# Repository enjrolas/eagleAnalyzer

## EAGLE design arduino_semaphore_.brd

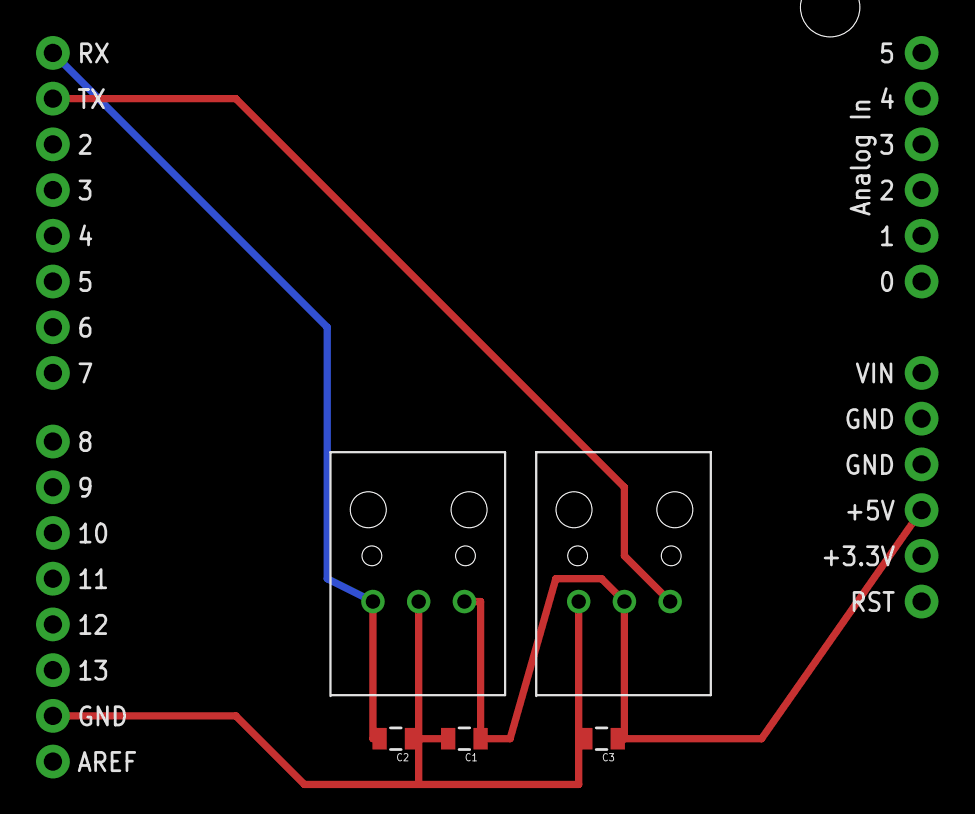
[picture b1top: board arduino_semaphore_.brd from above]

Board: 2 copper layers, 6 parts (0 on the bottom side), 4 nets.

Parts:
C1, C3: 0.1uF; 0805
C2: 30pF; 0805
U1: ARDUINO_SHIELDLABEL; DUEMILANOVE_SHIELD
U$1: DLR1160; DLR
U$2: DLT1160; DLT

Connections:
unnamed: C2.2, U1.RX, U$1.VOUT
unnamed: C1.1, C3.1, U1.5V, U$1.VCC, U$2.VCC
unnamed: C1.2, C2.1, C3.2, U1.GND@2, U$1.GND, U$2.GND
unnamed: U1.TX, U$2.VIN

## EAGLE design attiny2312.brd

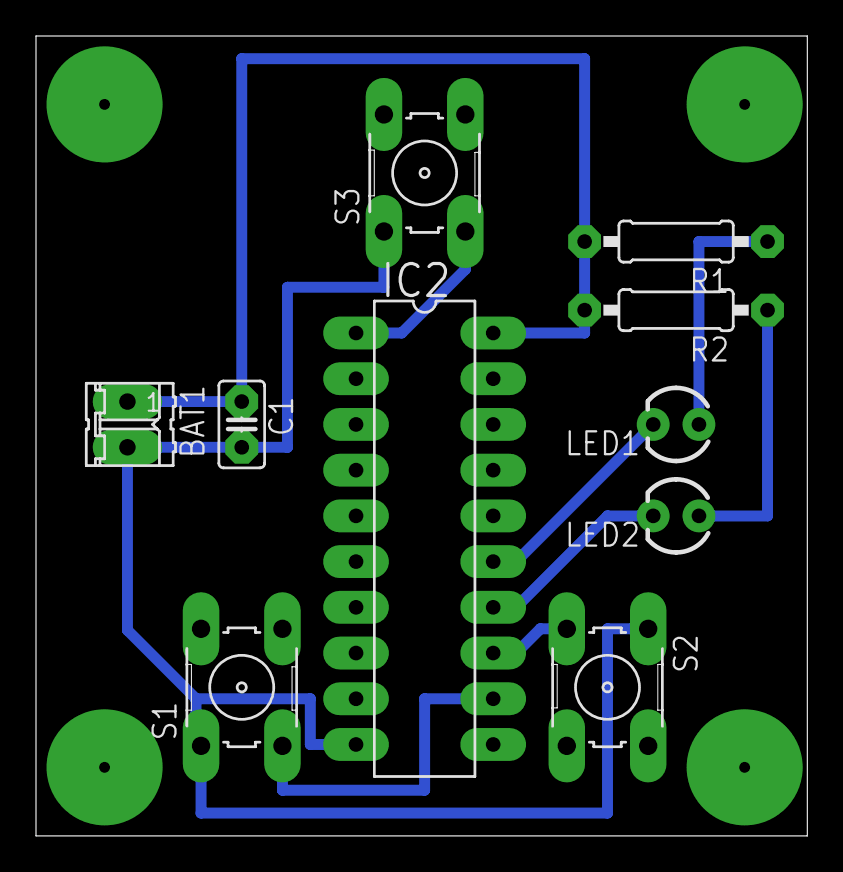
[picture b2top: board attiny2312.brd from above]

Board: 2 copper layers, 42.9 x 44.4 mm, 10 parts (0 on the bottom side), 9 nets.

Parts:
BAT1: 1.5 x 2; RELIMATE
C1: C2.5-2
IC2: AT90S2313P; DIL20
LED1, LED2: LED3MM
R1, R2: 0207/10
S1, S2, S3: B3F-10XX

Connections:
GND: BAT1.2, C1.2, IC2.10, S1.1, S2.1, S3.1
unnamed: LED1.A, R1.1
unnamed: LED2.A, R2.1
PB0: IC2.12, S1.3
PB1: IC2.13, S2.3
PB2: IC2.14, LED2.K
PB3: IC2.15, LED1.K
RESET: IC2.1, S3.3
VCC: BAT1.1, C1.1, IC2.20, R1.2, R2.2

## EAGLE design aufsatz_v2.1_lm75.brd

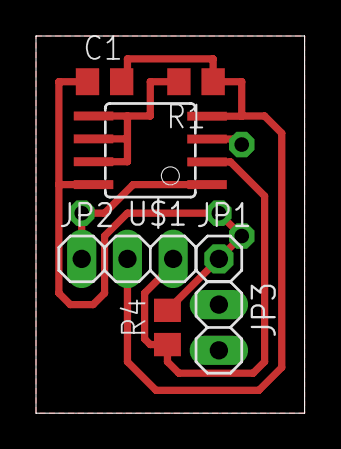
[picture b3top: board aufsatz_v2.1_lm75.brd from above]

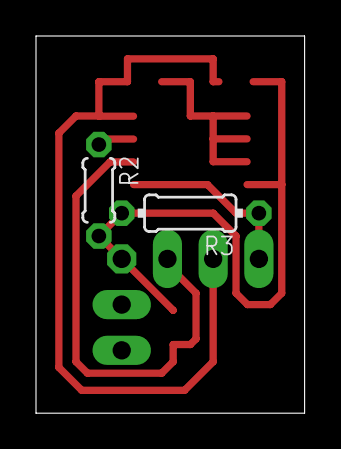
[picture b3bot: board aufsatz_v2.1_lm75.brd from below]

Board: 2 copper layers, 14.9 x 21.0 mm, 9 parts (2 on the bottom side), 6 nets.

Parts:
C1: 100n; C0805
JP1: 1X01
JP2: 1X03
JP3: 1X02
R1: 10k; R0805
R2: 10k; 0204/5
R3: 4k7; 0204/7
R4: 4k7; R0805
U$1: LM75; SOIC8

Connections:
GND: C1.2, JP2.2, R1.1, U$1.4
unnamed: R1.2, U$1.5, U$1.6, U$1.7
unnamed: R2.1, U$1.3
SCL: JP2.3, R4.1, U$1.2
SDA: JP2.1, R3.1, U$1.1
VCC: C1.1, JP1.1, R2.2, R3.2, R4.2, U$1.8

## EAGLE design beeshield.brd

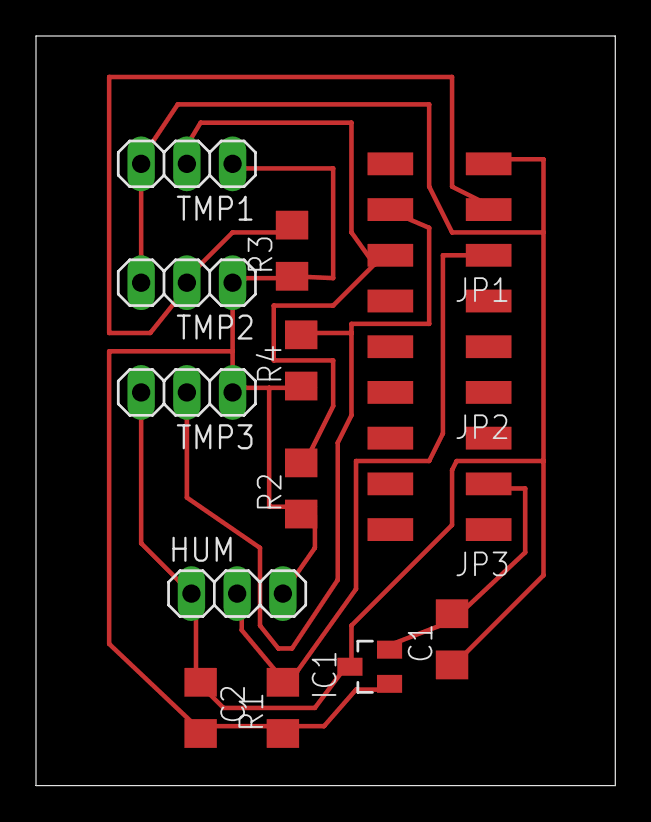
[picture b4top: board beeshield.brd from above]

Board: 2 copper layers, 32.2 x 41.6 mm, 14 parts (0 on the bottom side), 7 nets.

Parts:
C1, C2: 1206
HUM: 1X03
IC1: SOT23
JP1, JP2, JP3: 2X03SMD
R1: 10k; 1206
R2, R3, R4: 4k7; 1206
TMP1, TMP2, TMP3: 1X03

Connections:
GND: C1.1, C2.1, HUM.1, IC1.3, JP1.5, TMP1.3, TMP2.3, TMP3.3
IO0: HUM.2, JP1.1, R1.2
IO1: JP1.2, R2.2, TMP1.2
IO2: JP1.3, R3.2, TMP2.2
IO3: JP1.4, R4.2, TMP3.2
VBAT1: C1.2, IC1.2, JP3.3
VCC: C2.2, HUM.3, IC1.1, R1.1, R2.1, R3.1, R4.1, TMP1.1, TMP2.1, TMP3.1

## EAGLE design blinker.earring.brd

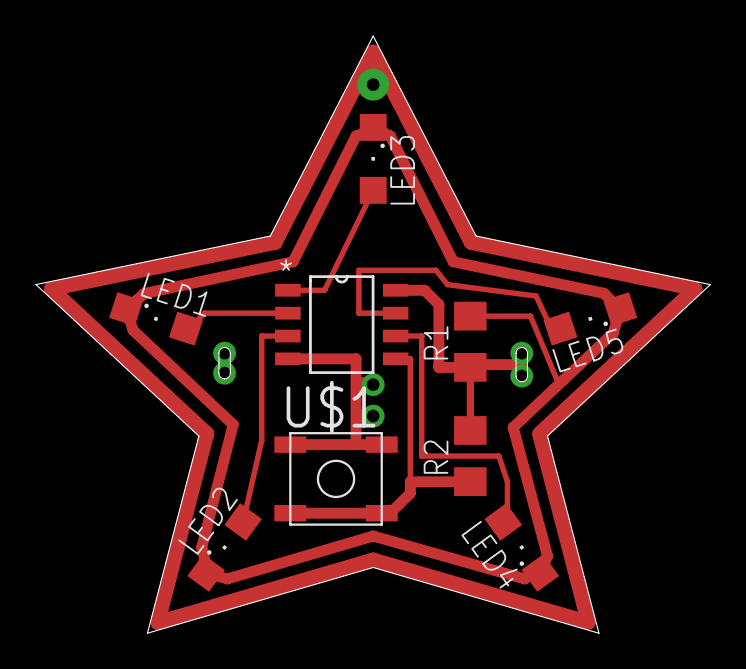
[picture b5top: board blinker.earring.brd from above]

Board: 2 copper layers, 37.5 x 33.2 mm, 9 parts (0 on the bottom side), 9 nets.

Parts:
LED1, LED2, LED3, LED4, LED5: SML1206
R1, R2: R1206
U$1: ATTINY13V-S8S1; ATTINY13A-SSU
U$3: MIMISMD; MINISMD

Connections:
unnamed: LED1.A, U$1.2
unnamed: LED2.A, U$1.3
unnamed: LED3.A, U$1.1
unnamed: LED4.A, U$1.6
unnamed: LED5.A, U$1.7
unnamed: U$1.4, U$3.P$1, U$3.P$3
unnamed: R1.1, R2.2, U$1.8
unnamed: LED1.C, LED2.C, LED3.C, LED4.C, LED5.C, R1.2
unnamed: R2.1, U$1.5, U$3.P$2, U$3.P$4

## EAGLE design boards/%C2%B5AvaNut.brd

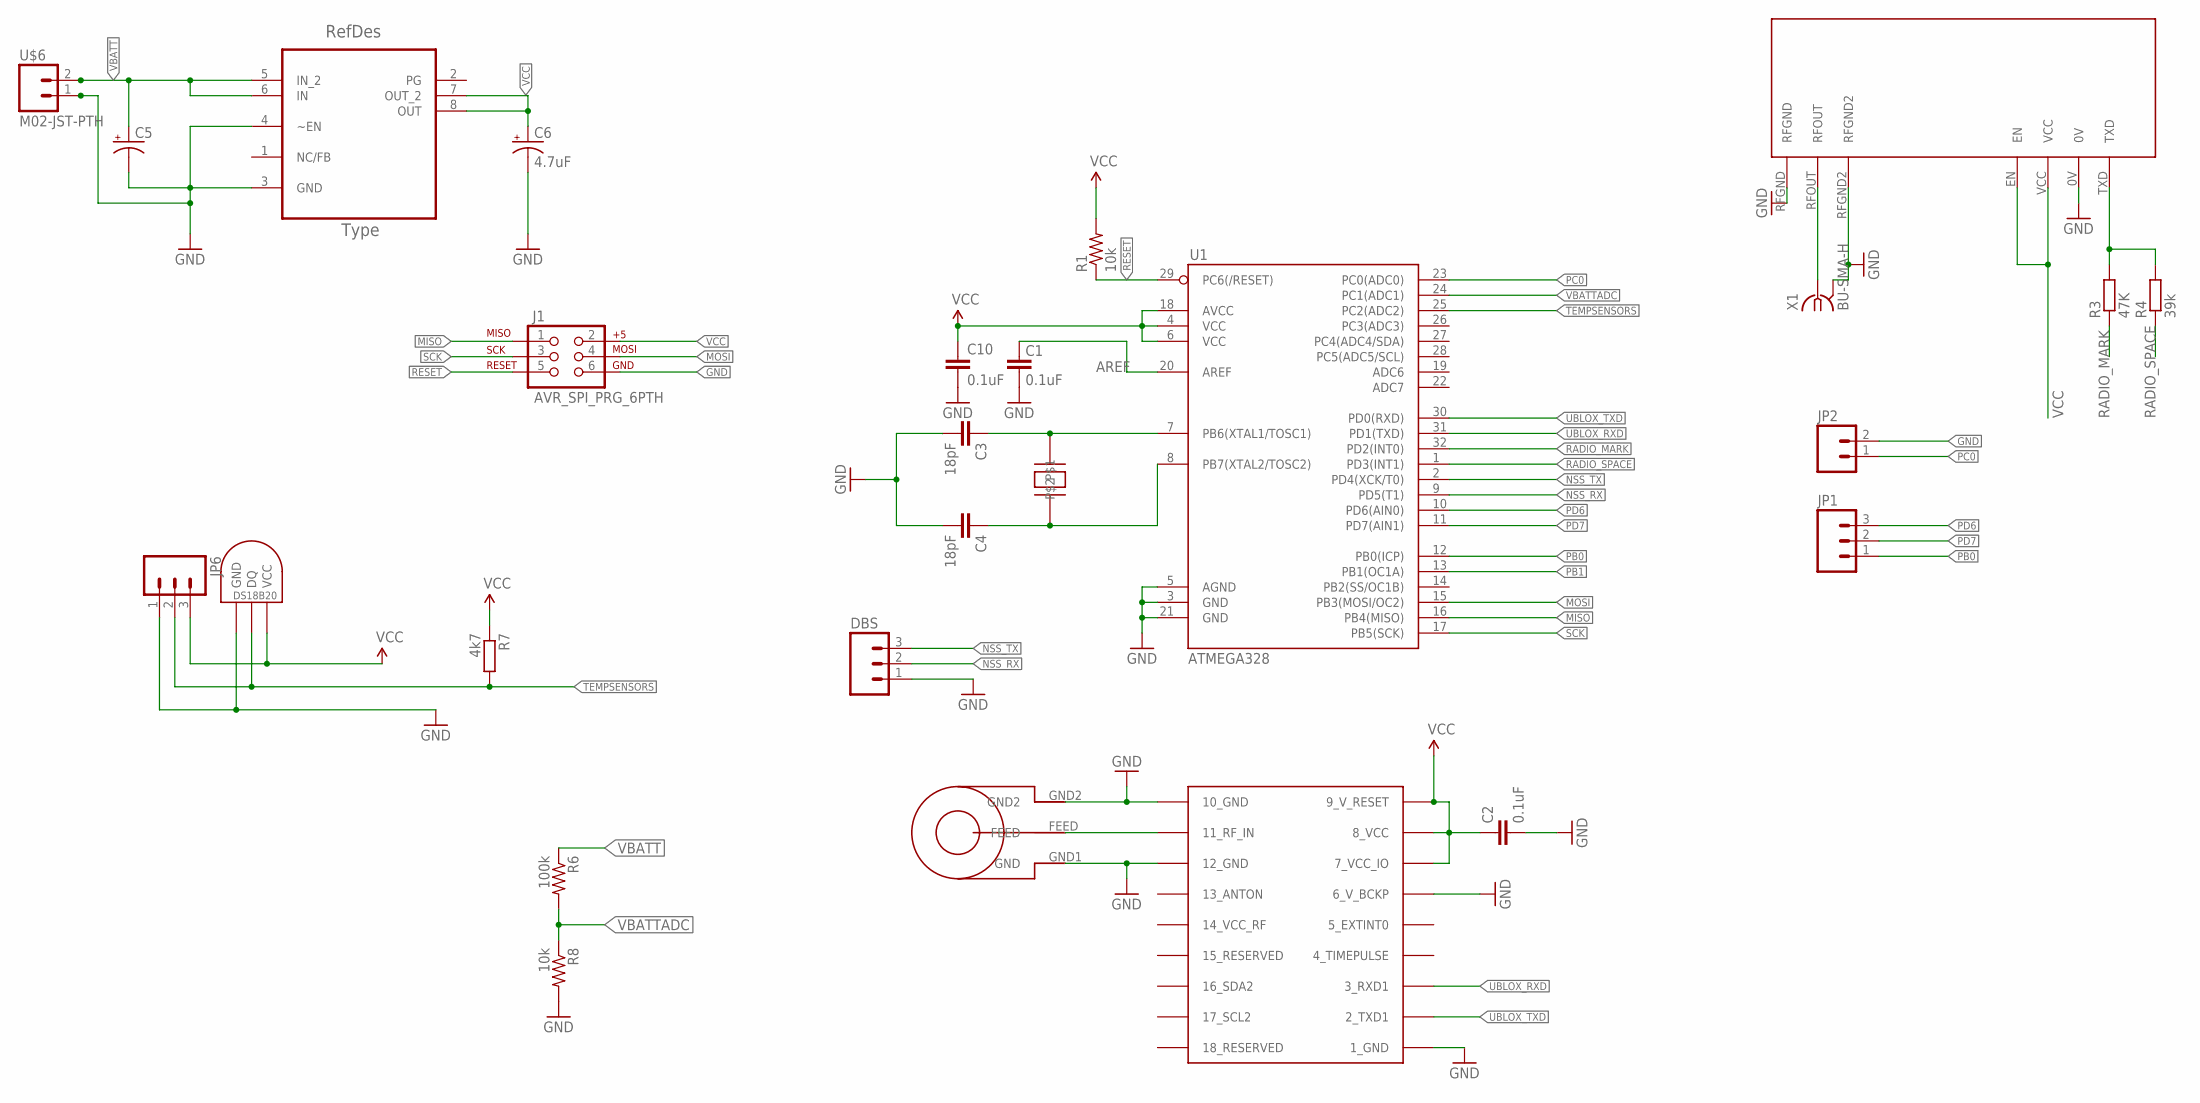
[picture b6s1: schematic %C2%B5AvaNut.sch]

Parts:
C1, C2, C10: 0.1uF; 0402-CAP
C3, C4: 18pF; 0402-CAP
C5: CAP_POL1206-KIT; EIA3216-KIT
C6: 4.7uF; EIA3216-KIT
DBS: M03PTH; 1X03
J1: AVR_SPI_PRG_6PTH; 2X3
JP1: M03POGO_PIN_HOLES_ONLY; 1X03_PP_HOLES_ONLY
JP2: M02POGO_PIN_HOLES_ONLY; 1X02_PP_HOLES_ONLY
JP6: M03JST-PTH; JST-3-PTH
NTX2TEMP: DS1821; DS18B20_SOIC
R1, R8: 10k; 0402-RES
R3: 47K; R0805
R4: 39k; R0805
R6: 100k; 0402-RES
R7: 4k7; R0805
U1: ATMEGA328; TQFP32-08
U2: TPS76633D; SOIC127P600X175-8N
U$1: UBLOX_MAX-6
U$2: ABRACON_ABM3_CRYSTAL
U$3: SARANTEL-SR1202
U$4: NTX2
U$6: M02-JST-PTH
X1: BU-SMA-H

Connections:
AREF: C1.2, U1.20 (AREF)
GND: C1.1, C2.2, C3.2, C4.2, C5.C (-), C6.C (-), C10.2, DBS.1, J1.6, JP2.2, JP6.1, NTX2TEMP.GND, R8.2, U1.3 (GND), U1.5 (AGND), U1.21 (GND), U2.3 (GND), U2.4 (~EN), U$1.1_GND, U$1.6_V_BCKP, U$1.10_GND, U$1.12_GND, U$3.GND1 (GND), U$3.GND2, U$4.0V, U$4.RFGND, U$4.RFGND2, U$6.1, X1.2 (GND), X1.3 (GND), X1.4 (GND), X1.5 (GND)
MISO: J1.1, U1.16 (PB4(MISO))
MOSI: J1.4, U1.15 (PB3(MOSI/OC2))
unnamed: U$4.RFOUT, X1.1
unnamed: R3.2, R4.2, U$4.TXD
unnamed: U$1.11_RF_IN, U$3.FEED
unnamed: C3.1, U1.7 (PB6(XTAL1/TOSC1)), U$2.P$2
unnamed: C4.1, U1.8 (PB7(XTAL2/TOSC2)), U$2.P$1
NSS_RX: DBS.2, U1.9 (PD5(T1))
NSS_TX: DBS.3, U1.2 (PD4(XCK/T0))
PB0: JP1.1, U1.12 (PB0(ICP))
PB1: U1.13 (PB1(OC1A))
PC0: JP2.1, U1.23 (PC0(ADC0))
PD6: JP1.3, U1.10 (PD6(AIN0))
PD7: JP1.2, U1.11 (PD7(AIN1))
RADIO_MARK: R3.1, U1.32 (PD2(INT0))
RADIO_SPACE: R4.1, U1.1 (PD3(INT1))
RESET: J1.5, R1.1, U1.29 (PC6(/RESET))
SCK: J1.3, U1.17 (PB5(SCK))
TEMPSENSORS: JP6.2, NTX2TEMP.DQ, R7.2, U1.25 (PC2(ADC2))
UBLOX_RXD: U1.31 (PD1(TXD)), U$1.3_RXD1
UBLOX_TXD: U1.30 (PD0(RXD)), U$1.2_TXD1
VBATT: C5.A (+), R6.1, U2.5 (IN_2), U2.6 (IN), U$6.2
VBATTADC: R6.2, R8.1, U1.24 (PC1(ADC1))
VCC: C2.1, C6.A (+), C10.1, J1.2, JP6.3, NTX2TEMP.VCC, R1.2, R7.1, U1.4 (VCC), U1.6 (VCC), U1.18 (AVCC), U2.7 (OUT_2), U2.8 (OUT), U$1.7_VCC_IO, U$1.8_VCC, U$1.9_V_RESET, U$4.EN, U$4.VCC

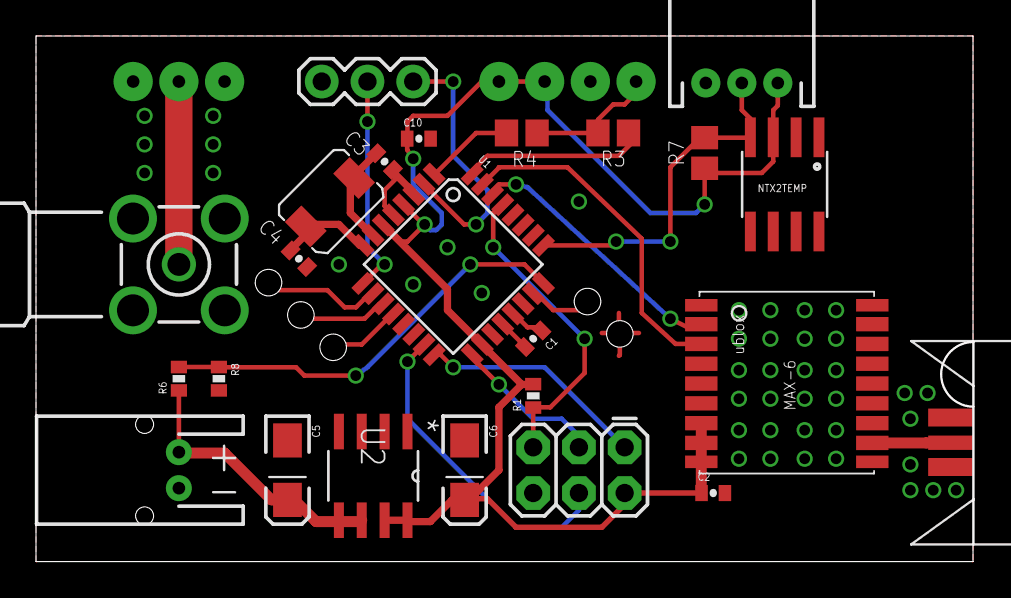
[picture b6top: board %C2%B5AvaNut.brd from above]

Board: 2 copper layers, 52.1 x 29.2 mm, 27 parts (1 on the bottom side), 25 nets.

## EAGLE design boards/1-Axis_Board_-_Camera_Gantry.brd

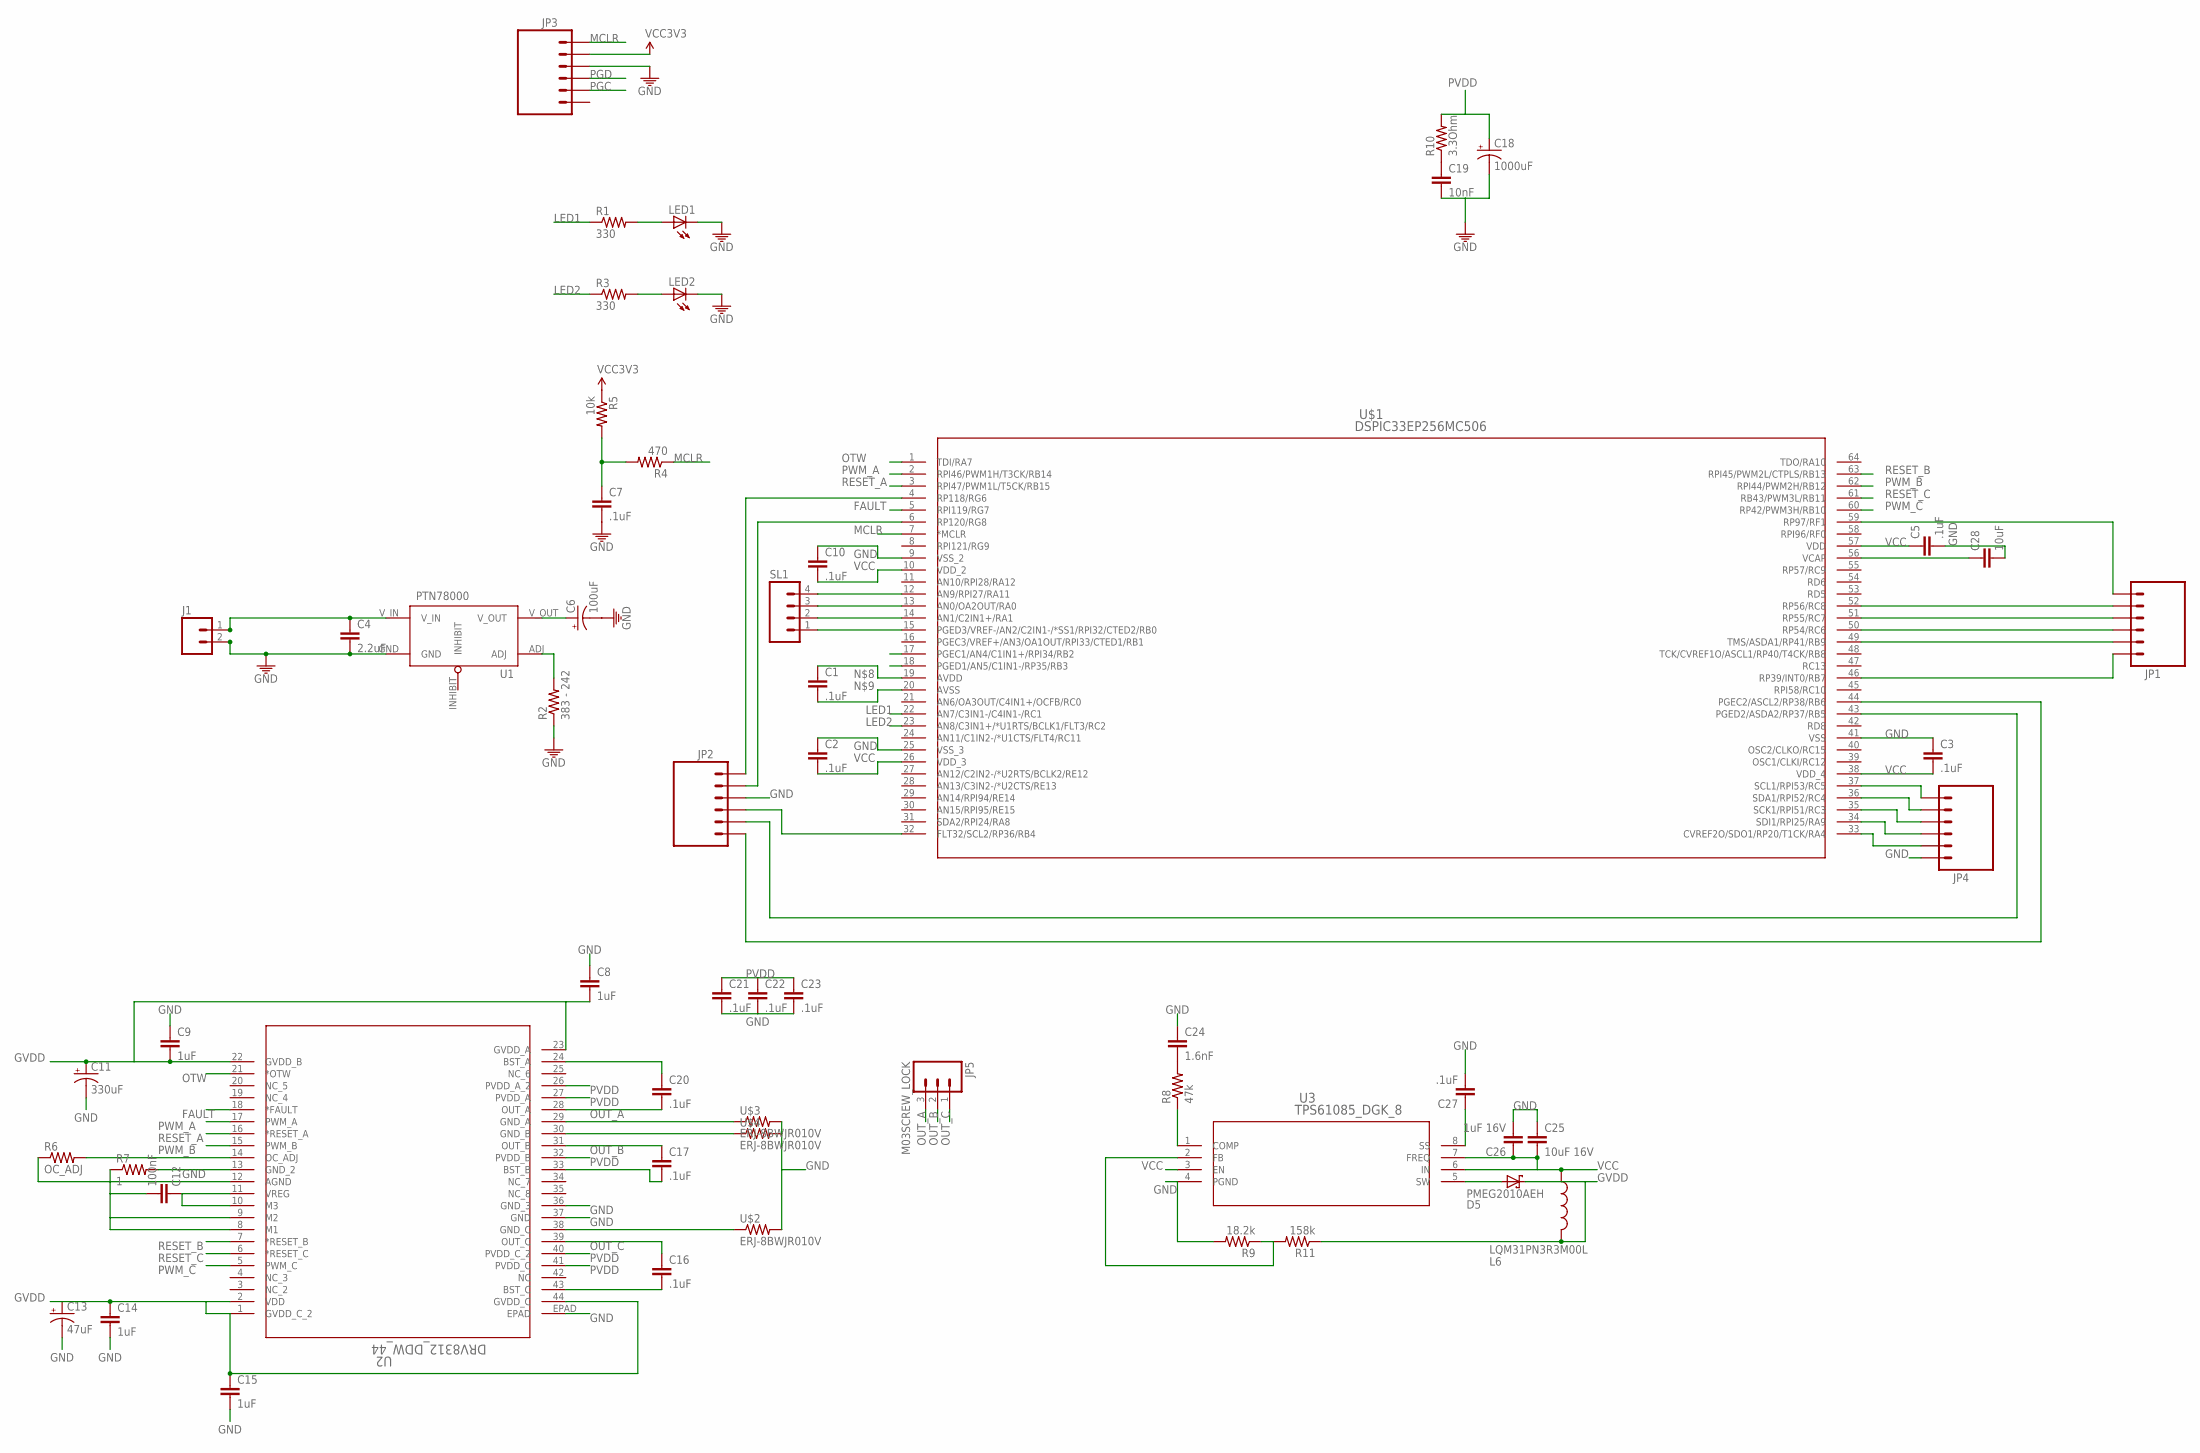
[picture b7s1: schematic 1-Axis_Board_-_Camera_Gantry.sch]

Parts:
C1, C2, C3, C5, C7, C10, C16, C17, C20, C21, C22, C23, C27: .1uF; 0805
C4: 2.2uF; 1206
C6: 100uF; CPOL-RADIAL-100UF-25V
C8, C9, C14, C15: 1uF; 0805
C11: 330uF; CPOL-RADIAL-1000UF-25V
C12: 100nF; 0805
C13: 47uF; CPOL-RADIAL-1000UF-25V
C18: 1000uF; CPOL-RADIAL-1000UF-25V
C19: 10nF; 0805
C24: 1.6nF; 0805
C25: 10uF 16V; 1206
C26: 1uF 16V; 0805
C28: 10uF; 1206
D5: PMEG2010AEH; SOD-123
J1: M023.5MM-NO_SILK; SCREWTERMINAL-3.5MM-2-NS
JP1, JP2, JP3, JP4: M06LOCK; 1X06_LOCK
JP5: M03SCREW_LOCK; SCREWTERMINAL-3.5MM-3_LOCK.007S
L6: LQM31PN3R3M00L; 1206
LED1, LED2: LED1206; LED-1206
R1, R3: 330; 0805
R2: 383 - 242; 0805
R4: 470; 0805
R5: 10k; 0805
R6: OC_ADJ; 0805
R7: 1; 0805
R8: 47k; 0805
R9: 18.2k; 0805
R10: 3.3Ohm; 0805
R11: 158k; 0805
SL1: M04LOCK; 1X04_LOCK
U1: PTN78000
U2: DRV8312_DDW_44; DDW44_8P26X4P31
U3: TPS61085_DGK_8; DGK8
U$1: DSPIC33EP256MC506; QFP64-10X10MC
U$2, U$3, U$4: ERJ-8BWJR010V; 1206

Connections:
FAULT: U2.18 (*FAULT), U$1.5 (RPI119/RG7)
GND: C2.1, C3.1, C4.2, C5.2, C6.2 (-), C7.2, C8.1, C9.1, C10.1, C11.2 (-), C13.2 (-), C14.2, C15.2, C18.2 (-), C19.2, C21.2, C22.2, C23.2, C24.1, C25.1, C26.2, C27.2, C28.2, J1.2 (1), JP2.3, JP3.3, JP4.1, LED1.C, LED2.C, R2.1, R7.2, R9.2, U1.GND, U2.13 (GND_2), U2.36 (GND_3), U2.37 (GND), U2.EPAD, U3.4 (PGND), U$1.9 (VSS_2), U$1.25 (VSS_3), U$1.41 (VSS), U$2.2, U$3.2, U$4.2
GVDD: C8.2, C9.2, C11.1 (+), C13.1 (+), C14.1, C15.1, D5.C, L6.2, R11.1, U2.1 (GVDD_C_2), U2.2 (VDD), U2.22 (GVDD_B), U2.23 (GVDD_A), U2.44 (GVDD_C)
LED1: R1.1, U$1.22 (AN7/C3IN1-/C4IN1-/RC1)
LED2: R3.1, U$1.23 (AN8/C3IN1+/*U1RTS/BCLK1/FLT3/RC2)
MCLR: JP3.1, R4.1, U$1.7 (*MCLR)
unnamed: LED1.A, R1.2
unnamed: C7.1, R4.2, R5.2
unnamed: LED2.A, R3.2
unnamed: U2.38 (GND_C), U$2.1
unnamed: U2.29 (GND_A), U$3.1
unnamed: R2.2, U1.ADJ
unnamed: U2.30 (GND_B), U$4.1
unnamed: C1.1, U$1.19 (AVDD)
unnamed: C1.2, U$1.20 (AVSS)
unnamed: C27.1, U3.8 (SS)
unnamed: R8.1, U3.1 (COMP)
unnamed: C24.2, R8.2
unnamed: C19.1, R10.1
unnamed: C28.1, U$1.56 (VCAP)
unnamed: D5.A, U3.5 (SW)
unnamed: R9.1, R11.2, U3.2 (FB)
unnamed: JP2.1, U$1.4 (RP118/RG6)
unnamed: JP2.4, U$1.32 (FLT32/SCL2/RP36/RB4)
unnamed: JP2.5, U$1.43 (PGED2/ASDA2/RP37/RB5)
unnamed: C16.2, U2.43 (BST_C)
unnamed: JP2.6, U$1.44 (PGEC2/ASCL2/RP38/RB6)
unnamed: JP1.1, U$1.46 (RP39/INT0/RB7)
unnamed: JP1.2, U$1.49 (TMS/ASDA1/RP41/RB9)
unnamed: JP1.3, U$1.50 (RP54/RC6)
unnamed: JP1.5, U$1.52 (RP56/RC8)
unnamed: JP1.6, U$1.59 (RP97/RF1)
unnamed: JP2.2, U$1.6 (RP120/RG8)
unnamed: C17.2, U2.33 (BST_B)
unnamed: JP1.4, U$1.51 (RP55/RC7)
unnamed: JP4.4, U$1.35 (SCK1/RPI51/RC3)
unnamed: JP4.5, U$1.36 (SDA1/RPI52/RC4)
unnamed: JP4.6, U$1.37 (SCL1/RPI53/RC5)
unnamed: JP4.3, U$1.34 (SDI1/RPI25/RA9)
unnamed: C20.1, U2.24 (BST_A)
unnamed: SL1.1, U$1.15 (PGED3/VREF-/AN2/C2IN1-/*SS1/RPI32/CTED2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)
unnamed: SL1.2, U$1.14 (AN1/C2IN1+/RA1)
unnamed: SL1.3, U$1.13 (AN0/OA2OUT/RA0)
unnamed: SL1.4, U$1.12 (AN9/RPI27/RA11)
unnamed: JP4.2, U$1.33 (CVREF2O/SDO1/RP20/T1CK/RA4)
unnamed: C12.2, R6.1, R7.1, U2.8 (M1), U2.9 (M2), U2.12 (AGND)
unnamed: C12.1, U2.10 (M3), U2.11 (VREG)
OC_ADJ: R6.2, U2.14 (OC_ADJ)
OTW: U2.21 (*OTW), U$1.1 (TDI/RA7)
OUT_A: C20.2, JP5.3, U2.28 (OUT_A)
OUT_B: C17.1, JP5.2, U2.31 (OUT_B)
OUT_C: C16.1, JP5.1, U2.39 (OUT_C)
PGC: JP3.5, U$1.17 (PGEC1/AN4/C1IN1+/RPI34/RB2)
PGD: JP3.4, U$1.18 (PGED1/AN5/C1IN1-/RP35/RB3)
PVDD: C4.1, C18.1 (+), C21.1, C22.1, C23.1, J1.1 (2), R10.2, U1.V_IN, U2.26 (PVDD_A_2), U2.27 (PVDD_A), U2.32 (PVDD_B), U2.40 (PVDD_C_2), U2.41 (PVDD_C)
PWM_A: U2.17 (PWM_A), U$1.2 (RPI46/PWM1H/T3CK/RB14)
PWM_B: U2.15 (PWM_B), U$1.62 (RPI44/PWM2H/RB12)
PWM_C: U2.5 (PWM_C), U$1.60 (RP42/PWM3H/RB10)
RESET_A: U2.16 (*RESET_A), U$1.3 (RPI47/PWM1L/T5CK/RB15)
RESET_B: U2.7 (*RESET_B), U$1.63 (RPI45/PWM2L/CTPLS/RB13)
RESET_C: U2.6 (*RESET_C), U$1.61 (RB43/PWM3L/RB11)
VCC: C2.2, C3.2, C5.1, C6.1 (+), C10.2, C25.2, C26.1, L6.1, U1.V_OUT, U3.3 (EN), U3.6 (IN), U3.7 (FREQ), U$1.10 (VDD_2), U$1.26 (VDD_3), U$1.38 (VDD_4), U$1.57 (VDD)
VCC3V3: JP3.2, R5.1

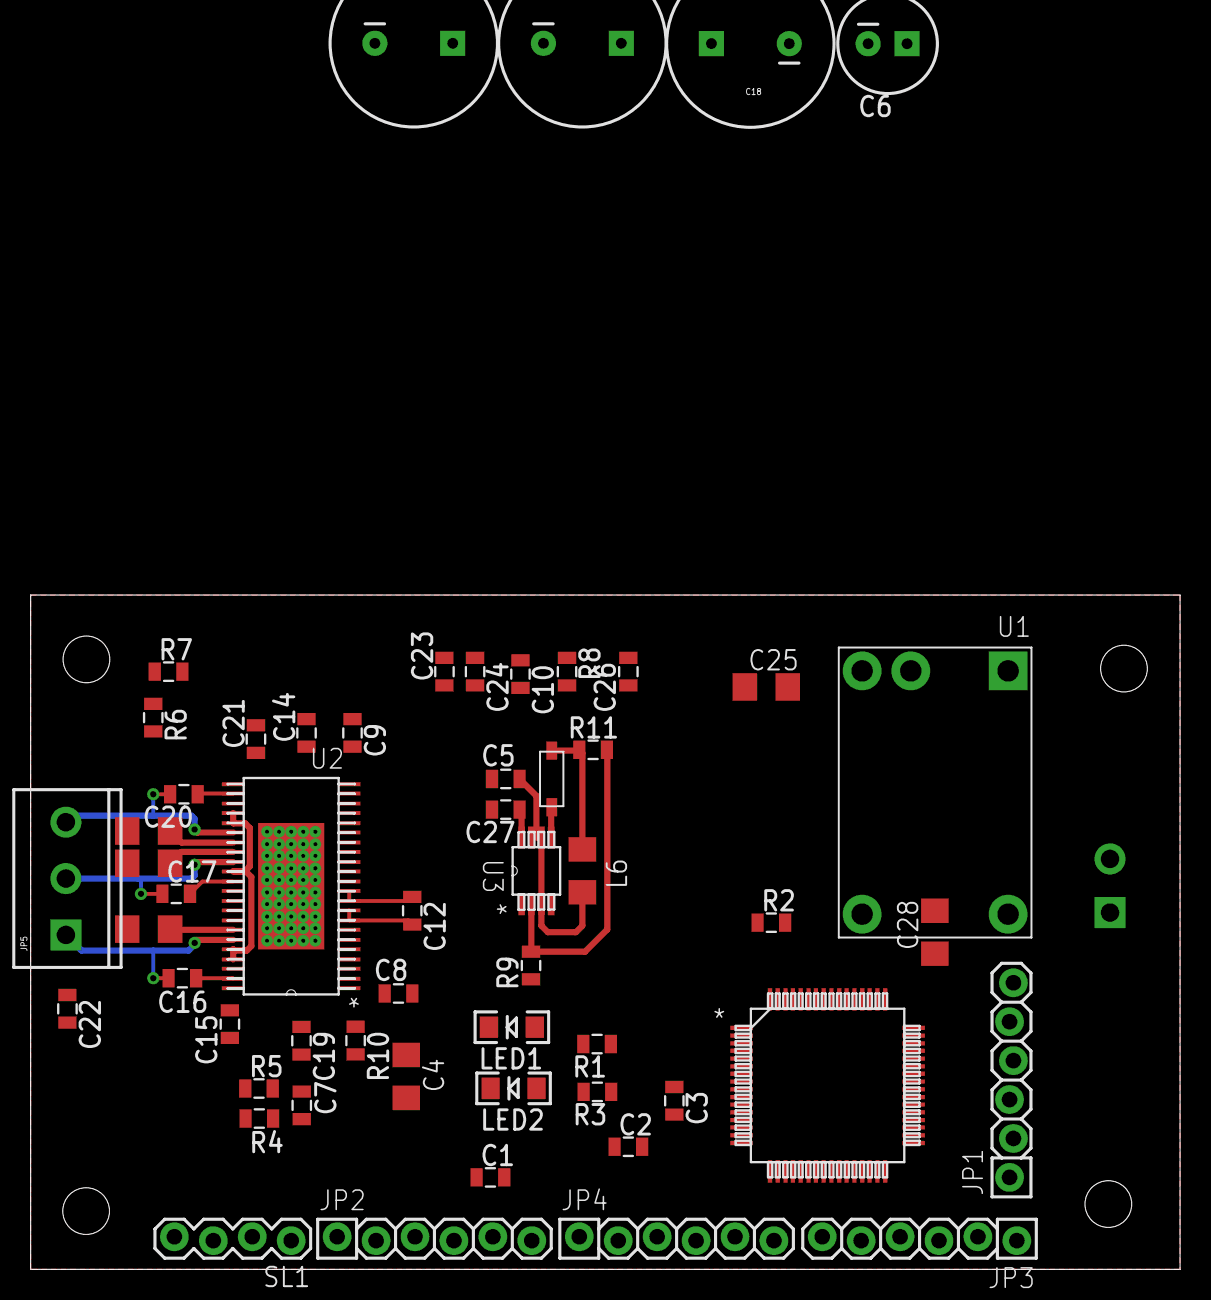
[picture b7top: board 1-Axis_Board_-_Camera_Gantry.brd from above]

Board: 2 copper layers, 75.0 x 44.0 mm, 61 parts (0 on the bottom side), 63 nets.

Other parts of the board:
E$1, E$2, E$3, E$4: STAND-OFF-TIGHT

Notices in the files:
parts and their libraries:
SparkFun-Boards: Licensing: CC v3.0 Share-Alike You are welcome to use this library for commercial purposes.
